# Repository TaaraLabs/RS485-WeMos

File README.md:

RS485-WeMos
===========

RS-485 Shield for WeMos D1

[Official WebSite](https://taaralabs.eu/rw1)

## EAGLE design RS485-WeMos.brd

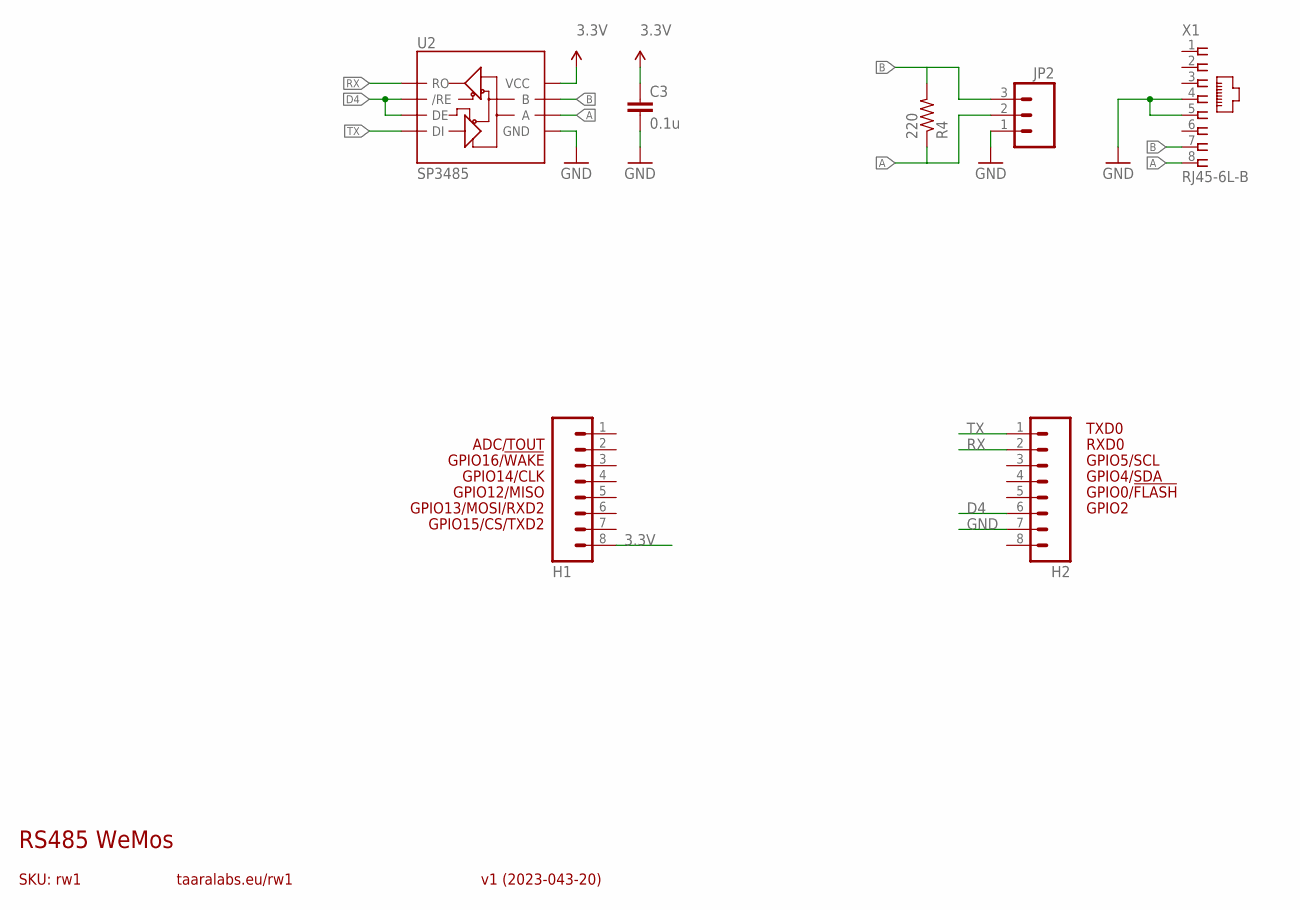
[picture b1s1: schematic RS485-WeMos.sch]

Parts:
C3: 0.1u; 0603-CAP
H1, H2: M08; 1X08
JP2: M03SCREW; SCREWTERMINAL-3.5MM-3
R4: 220; 0603-RES
U2: SP3485; SO08
X1: RJ45-6L-B; RJ45-NO-SHIELD

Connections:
3.3V: C3.1, H1.8, U2.8 (VCC)
A: JP2.2, R4.1, U2.6 (A), X1.8
B: JP2.3, R4.2, U2.7 (B), X1.7
D4: H2.6, U2.2 (/RE), U2.3 (DE)
GND: C3.2, H2.7, JP2.1, U2.5 (GND), X1.4, X1.5
RX: H2.2, U2.1 (RO)
TX: H2.1, U2.4 (DI)

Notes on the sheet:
GPIO2
GPIO0/!FLASH
GPIO12/MISO
GPIO4/SDA
GPIO5/SCL
RXD0
TXD0
GPIO13/MOSI/RXD2
GPIO14/CLK
GPIO15/CS/TXD2
GPIO16/!WAKE
SKU: rw1
RS485 WeMos
v1 (2023-043-20)
taaralabs.eu/rw1
ADC/TOUT

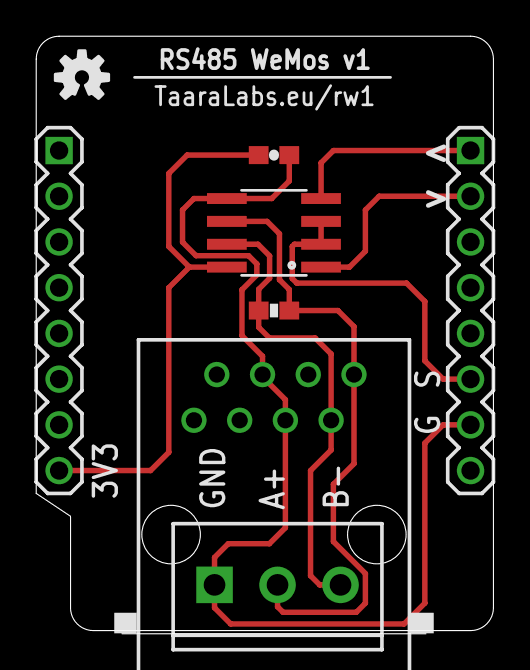
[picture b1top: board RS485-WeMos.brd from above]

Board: 2 copper layers, 25.4 x 33.0 mm, 9 parts (1 on the bottom side), 7 nets.

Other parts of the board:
U$1, U$2: OSHW-LOGO-S

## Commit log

2023-03-21 Design files added
2023-03-21 Images added
2023-04-07 Esphome ModBus example
2023-04-07 example file renamed
2023-04-28 renamed to be more specific
2023-04-28 Added example for 16 channel Current Transformer from AliExpress
2023-07-01 added flow control pin for D1 Mini

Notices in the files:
parts and their libraries:
freetronics-original: Licensing: CC v3.0 Share-Alike You are welcome to use this library for commercial purposes.
SparkFun-Capacitors: Licensing: Creative Commons ShareAlike 4.0 International - https://creativecommons.org/licenses/by-sa/4.0
